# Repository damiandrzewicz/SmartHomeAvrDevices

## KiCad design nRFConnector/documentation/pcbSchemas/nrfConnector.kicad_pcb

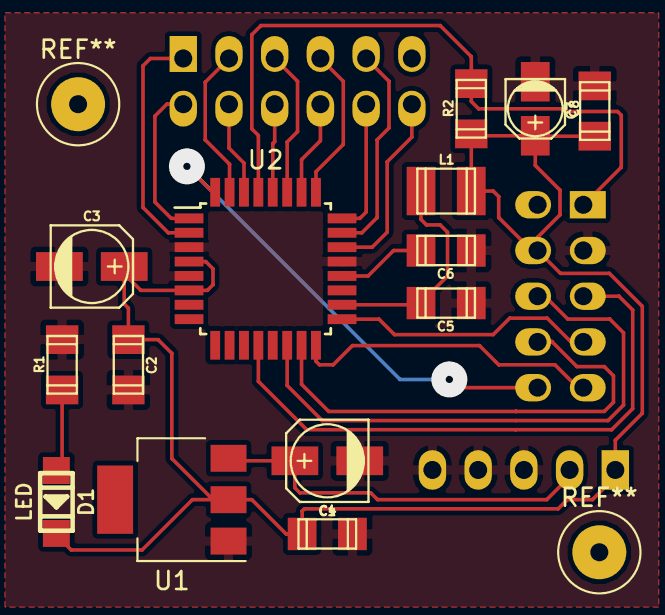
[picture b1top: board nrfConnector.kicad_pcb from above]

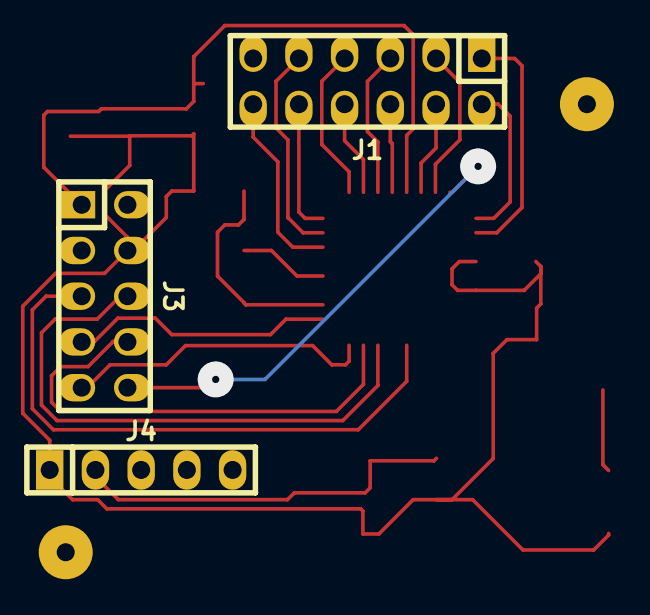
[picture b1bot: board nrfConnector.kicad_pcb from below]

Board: 2 copper layers, 17 parts (3 on the bottom side), 24 nets.

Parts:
C1, C3: 22uF; c_elec_4x5.3
C2, C4, C5, C6: 100nF; c_1206
C7: 10nF; c_1206
C8: 4.7uF; c_elec_3x5.3
D1: LED; Led_1206
J1: HEADER_6x2; pin_strip_6x2
J3: HEADER_5x2; pin_strip_5x2
J4: HEADER_5; pin_strip_5
L1: 10uH; c_1210
R1: 200R; r_1206
R2: 10k; r_1206
U1: LM1117-3.3; SOT-223
U2: ATMEGA8-16AU; TQFP-32_7x7mm_Pitch0.8mm

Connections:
+3V3: C2.2, C3.1, C4.2, C7.2, C8.1, D1.2, J3.4, J4.1, L1.1, R2.2, U1.2, U2.4, U2.6
+5V: C1.1, J4.2, U1.3
ADC7: J1.12, U2.22
CE: J3.5, U2.12
CSN: J3.6, U2.14
GND: C1.2, C2.1, C3.2, C4.1, C5.2, C6.2, C7.1, C8.2, J3.3, J4.3, J4.4, J4.5, R1.1, U1.1, U2.3, U2.5, U2.21
IRQ: J3.10, U2.32
MISO: J3.9, U2.16
MOSI: J3.8, U2.15
unnamed: C5.1, L1.2, U2.18
unnamed: C6.1, U2.20
unnamed: D1.1, R1.2
PC0: J1.9, U2.23
PC1: J1.10, U2.24
PC2: J1.7, U2.25
PC3: J1.8, U2.26
PC4: J1.5, U2.27
PC5: J1.6, U2.28
PD3: J1.2, U2.1
PD4: J1.1, U2.2
RST: J3.1, R2.1, U2.29
RX: J1.4, U2.30
SCK: J3.7, U2.17
TX: J1.3, U2.31

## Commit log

2018-06-03 Changed error handling
2018-06-05 Changed controllers
    - added new controllers for Master and Slave transmitters,
    - changed AVR clock to 8MHz
2018-06-05 Project tree change
    - created new folder for storing project sources
2018-06-06 New controller
    - added standalone controller
    - implemented and cleaned base and master controller
2018-06-16 Changes in controllers
    implemented new controller handling
2018-06-16 Implementation of WindowDriver
    - implemented parsing data from internal connector (sending and receiving),
    - created servo objects
    - created servo events
    - created parser events
    - created quadrature encoders objects
2018-06-16 Safe commit
2018-06-19 Reimplementation changes
    Changed processing internal Uart messages
2018-07-09 Implementation
2018-09-09 Remove ParserLib library
2018-09-09 Remove nRFConnector project
2018-09-09 Changes for Window Driver
2018-09-09 modified gitignore
2018-09-09 modified Readme
2018-09-09 New ParseLib library
2018-09-09 New ConnectorRF24 library
2018-09-09 Implementation for sending radio and uart data
2018-09-20 Implemented sending and receiving messages for TerminalController
2018-09-20 Started proper implementation for WindowDriver
2018-09-22 Implementation for Window driver for receiving messages from connector
2018-09-23 Added processing requests in WindowDriver
2018-10-21 new requests and responses implementation for window driver
2018-10-25 compatibility with tester app
2018-10-30 Changed \ok\response to $ok$\-compatibility with testing app
2018-11-05 Implementation for two-directional communication for connectors
2018-11-07 Partial implementation for manual driving servo and programmatically sterting nrf24l01
2018-11-10 calibration
2018-11-11 Saving data in EEPROM
2018-11-14 Something new implemented
2018-11-19 ADC, open/close blind algorithm
2018-12-02 Nearly final verison of blind driving
